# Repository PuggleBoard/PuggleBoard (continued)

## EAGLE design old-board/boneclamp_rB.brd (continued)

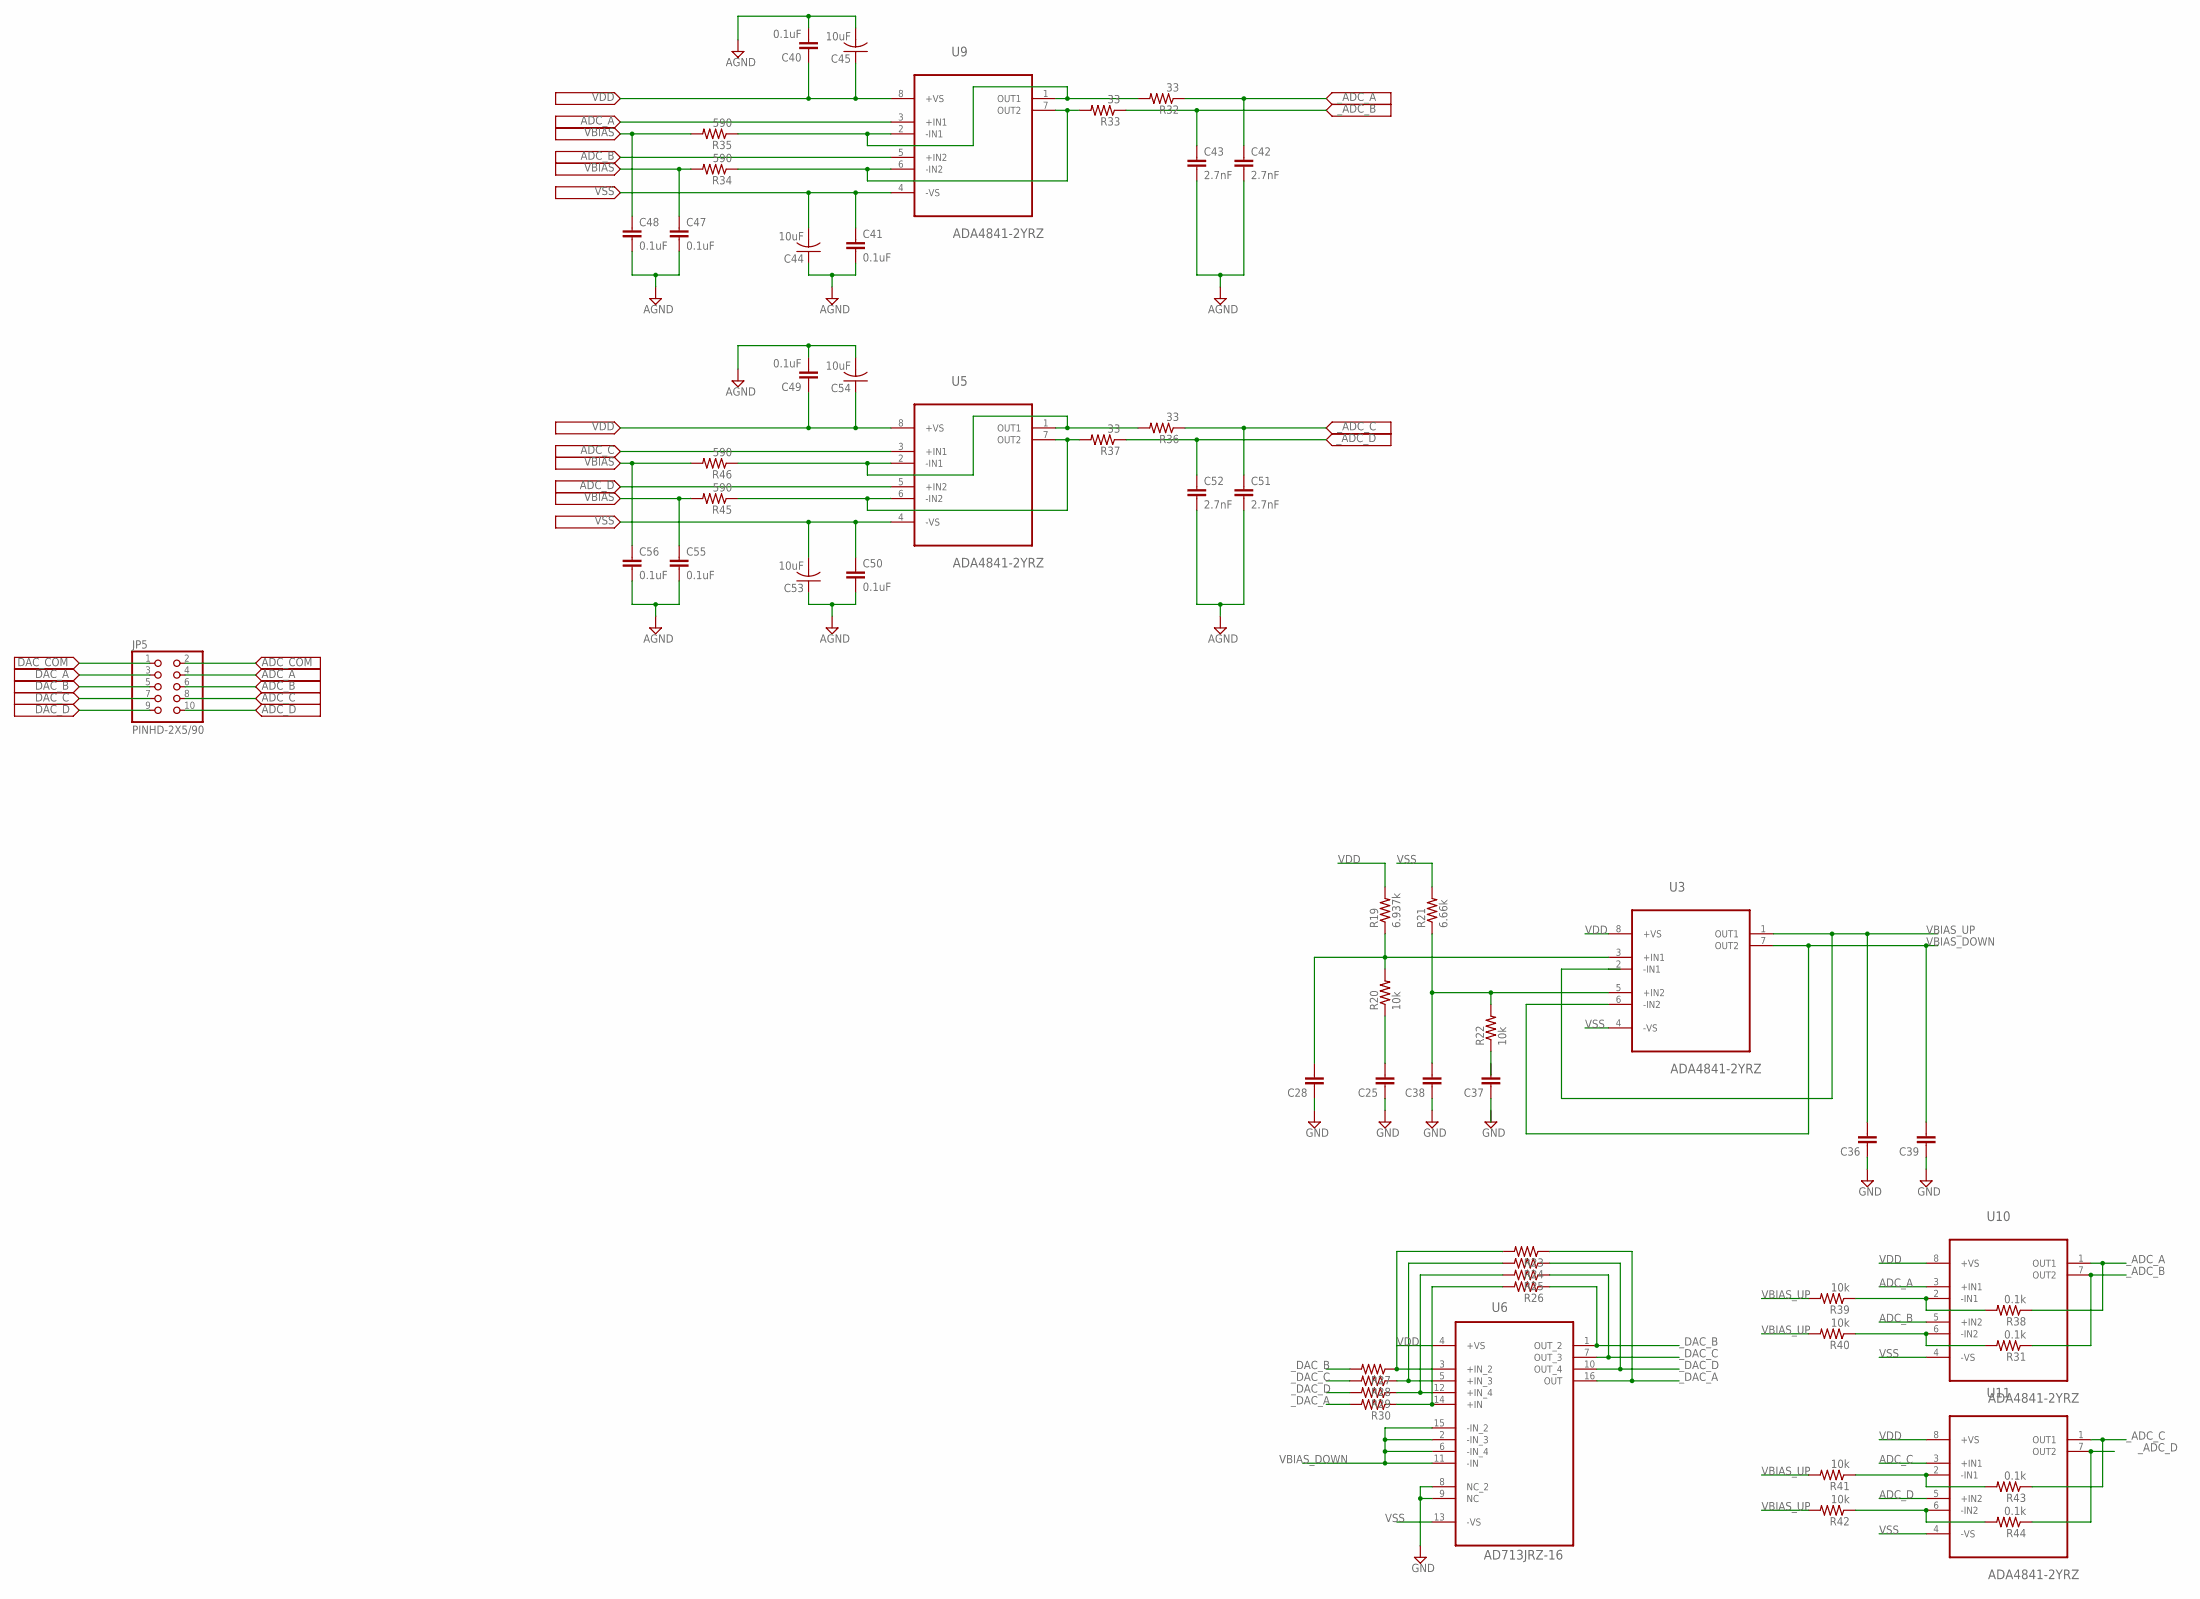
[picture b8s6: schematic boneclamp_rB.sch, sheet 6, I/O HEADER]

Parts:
C25, C28, C36, C37, C38, C39: C-EU025-025X050; C025-025X050
C40, C41, C47, C48, C49, C50, C55, C56: 0.1uF; C0805
C42, C43, C51, C52: 2.7nF; C0805
C44, C45, C53, C54: 10uF; C0805
JP5: PINHD-2X5/90; 2X05/90
R19: 6.937k; 0204V
R20, R22: 10k; 0204V
R21: 6.66k; 0204V
R23, R24, R25, R26, R27, R28, R29, R30: R-US_0204/2V; 0204V
R31, R38, R43, R44: 0.1k; R0805
R32, R33, R36, R37: 33; R0603
R34, R35, R45, R46: 590; R0603
R39, R40, R41, R42: 10k; R0805
U3, U5, U9, U10, U11: ADA4841-2YRZ; SOIC127P600X175-8N
U6: AD713JRZ-16; SOIC127P1032X265-16N

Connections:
ADC_A: JP5.4, U9.3 (+IN1), U10.3 (+IN1)
ADC_B: JP5.6, U9.5 (+IN2), U10.5 (+IN2)
ADC_C: JP5.8, U5.3 (+IN1), U11.3 (+IN1)
ADC_COM: JP5.2
ADC_D: JP5.10, U5.5 (+IN2), U11.5 (+IN2)
AGND: C40.2, C41.2, C42.2, C43.2, C44.1, C45.2, C47.2, C48.2, C49.2, C50.2, C51.2, C52.2, C53.1, C54.2, C55.2, C56.2; also elsewhere on the board
DAC_A: JP5.3
DAC_B: JP5.5
DAC_C: JP5.7
DAC_COM: JP5.1
DAC_D: JP5.9
GND: C25.1, C28.1, C36.1, C38.1, C39.1, U6.8 (NC_2), U6.9 (NC); also elsewhere on the board
unnamed: R37.2, R45.1, U5.6 (-IN2), U5.7 (OUT2)
unnamed: R33.2, R34.1, U9.6 (-IN2), U9.7 (OUT2)
unnamed: R26.2, R30.1, U6.14 (+IN)
unnamed: R36.2, R46.1, U5.1 (OUT1), U5.2 (-IN1)
unnamed: R32.2, R35.1, U9.1 (OUT1), U9.2 (-IN1)
unnamed: R25.2, R29.1, U6.12 (+IN_4)
unnamed: C38.2, R21.1, R22.2, U3.5 (+IN2)
unnamed: C28.2, R19.1, R20.2, U3.3 (+IN1)
unnamed: R24.2, R28.1, U6.5 (+IN_3)
unnamed: R23.2, R27.1, U6.3 (+IN_2)
unnamed: C25.2, R20.1
VBIAS: C47.1, C48.1, C55.1, C56.1, R34.2, R35.2, R45.2, R46.2; also elsewhere on the board
VBIAS_DOWN: C39.2, U3.6 (-IN2), U3.7 (OUT2), U6.2 (-IN_3), U6.6 (-IN_4), U6.11 (-IN), U6.15 (-IN_2)
VBIAS_UP: C36.2, R31.2, R38.2, R39.1, R39.2, R40.1, R40.2, R41.1, R41.2, R42.1, R42.2, R43.2, R44.2, U3.1 (OUT1), U3.2 (-IN1), U10.2 (-IN1), U10.6 (-IN2), U11.2 (-IN1), U11.6 (-IN2)
VDD: C40.1, C45.1, C49.1, C54.1, R19.2, U3.8 (+VS), U5.8 (+VS), U6.4 (+VS), U9.8 (+VS), U10.8 (+VS), U11.8 (+VS); also elsewhere on the board
VSS: C41.1, C44.2, C50.1, C53.2, R21.2, U3.4 (-VS), U5.4 (-VS), U6.13 (-VS), U9.4 (-VS), U10.4 (-VS), U11.4 (-VS); also elsewhere on the board
_ADC_A: C42.1, R32.1, R38.1, U10.1 (OUT1); also elsewhere on the board
_ADC_B: C43.1, R31.1, R33.1, U10.7 (OUT2); also elsewhere on the board
_ADC_C: C51.1, R36.1, R43.1, U11.1 (OUT1); also elsewhere on the board
_ADC_D: C52.1, R37.1, R44.1, U11.7 (OUT2); also elsewhere on the board
_DAC_A: R23.1, R30.2, U6.16 (OUT); also elsewhere on the board
_DAC_B: R26.1, R27.2, U6.1 (OUT_2); also elsewhere on the board
_DAC_C: R25.1, R28.2, U6.7 (OUT_3); also elsewhere on the board
_DAC_D: R24.1, R29.2, U6.10 (OUT_4); also elsewhere on the board

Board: 4 copper layers, 136 parts (0 on the bottom side), 59 nets, no tracks yet.

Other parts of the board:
U$77: ADS8343; SOP63P500X150-16N

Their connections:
GND: U$77.10, U$77.11; also elsewhere on the board
VCC: U$77.1, U$77.9

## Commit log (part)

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2013-02-24 Renamed the pcb folder to be more in line with other directory names
2013-02-24 Started working through the basic wiring on the schematic, connectrating on grounds, power, and analog IO
2013-02-27 I put an anti-aliasing filter design tool, provided by TI, into the PCB folder. The stop frequency (the frequency at which the attenuation is equal to the noise floor of the ADC (NOT the -3 dB point)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
2013-03-03 Found a good regulator for powering the BB using the +/- 6 to 12 volt rails required to use the boneclamp. Updated schematic and added data sheet to data-sheets folder
2013-03-03 Renamed file
2013-03-03 Added EEPROM to the I2C2bus to follow standard daughter board device ID requirements
2013-03-03 Added external 2.5 volt references for DAC and ADC. This circuit needs a buffer option which can be feed into the 3 position jumper.
2013-03-09 Moved the proto list directory to its proper location
2013-03-09 More changes to circuit
2013-03-09 Orgnanized data sheets
2013-03-09 Worked a bit on the schematic
2013-03-10 Added extended linear technologies library
2013-03-10 Added data sheet for +5V LDO reg.
2013-03-10 Minor schematic edit
2013-03-11 Added data sheets for the smd-to-dip adapters we will use. Minor changes to schematic
2013-03-12 Moved BOMs to their own directory
2013-03-13 Updated adafruit library with 2X5 0.1 inch pitch header, which we will use for I/O on the BC. Added that to the schematic
2013-03-14 Added buffered VREF divider, which feeds back into ADC to get bipolar input swing.
2013-03-14 Removed obsolete design-notes file
2013-03-15 Minor fixed to EEPROM circuit and ADC VREF buffer. Stephano, don't kill me.
2013-03-15 Added evaluation board PDFs to the data-sheets folder
2013-03-17 Minor edit
2013-03-18 Added p6 to the schematic of the BB, update the BC shematic and board
2013-03-19 Added Ground and power plane to pcb. Power plane will need to be split into primarly VDD and then a bit at the front of the board for VSS. VDD and VSS planes should not overlap in the Z direction.
2013-03-23 Added Stefano's biasing circuitry back into the master branch schematic. Automatic merge was not going to work properly
2013-03-23 Fixed the input biasing scheme. The op-amps we are using require -0.25 to 5.2 volt supply range to push the inputs into the 0 to 4.096 range required by the ADC. This means that our positive rail is 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
2013-03-23 Added pinout info for the bus pirate. Created a logic-sniffer project to examine the SPI signals sent to the chips. DAC is working nicely.
2013-03-24 Added information on the lm2663 DC-DC switch capacitor voltage inverter. A much better option than the inductor based inverter we are currently using.
2013-03-25 Added yet another option to explore for the ADC. I need to make some calls to find out what the best option is. There is always something wrong with any particular choice.
2013-03-26 Added the 8331 to schematic. I'm pretty sure this is the right ADC.
2013-03-27 Added excellent choice for external 2.048 VREF. This data sheet includes the circuit for creating a bipolar reference.
2013-03-31 Added data sheet for MCP8024 in the proto folder. This ADC will be helpful for troubleshooting the SPI interface since it is low cost and easy to play with.
2013-04-01 Finished basics of input stage to new 8331 and some of the digital interface for it.
2013-04-01 Minor changes.
2013-04-06 Tagged v0.1 as the last version to contain an effort to implement daisy chaining. This can serve as point of reference if we want to revisit that in the future.
2013-04-06 Cleaned up schematic to get it ready for actual component selection (passive commoponent packages) and final wiring.
2013-04-06 Replaced negative LDO with the MAX1735.
2013-04-07 Uninverted DAC output bias, found alternative amp
2013-04-07 Nearly finished with full circuit.I need the GPIO pins that we will be using.
2013-04-08 Minor schematic changes.
2013-04-18 Repackaged passive components.
    Shrank all passive components, verified their viability.
2013-04-19 Took care of most of Amanda's comments. Started using data buses instead of individual nets for the SPI interfaces.
2013-04-20 Started renaming test points, etc.
2013-04-20 Started getting rid of signal tag symbols, take too much room and cause problems with automatic component renumbering.
2013-04-20 Schematic nearly done. Checking/updating BOM.
2013-04-20 Finished BOM.
2013-04-20 Started layout.
2013-04-21 Finished switching voltage inverter layout.
2013-04-21 Added split GND plane.
2013-04-26 Committed breakout board
2013-05-02 Started laying out the AO buffer stage.
2013-05-02 Minore changes.
2013-05-03 Finalizing DAC/ADC buffer layout.
2013-05-03 Halfway through analog filters.
2013-05-04 Working on mixed signal ICs/
2013-05-04 Fixed the ground planes.
2013-05-06 DAC bypassing complete.
2013-05-09 Started to route IC groups together.
2013-05-10 More routing.
2013-05-10 Routing almost complete.
2013-05-11 Finished first intetation of routing! Need to clean up the silkscreen, check for single ended wires, double check schematic wiring, run DRC, and send it to fab.
2013-05-12 Fixed some random problems with the silkscreen.
2013-05-12 More minor silkscreen issues. Started drawing logo.
2013-05-12 Adding 4th DAC SPI pin on GPIO1_13
2013-05-12 Re-added the DAC SDO line.
2013-05-12 Added logo to board.
2013-05-12 Created CAM job to work with OSH Park.
2013-05-12 Reorganizing.
2013-05-12 Renamed the board.
2013-05-12 Finished the silkscreen stuff.
2013-05-13 Updated readme.
2013-05-15 Finished BOB.
2013-05-16 Finished BOB, created gerber files.
2013-05-16 Name change because versioning should happen via tags, not file names.
2013-05-16 Minor.
2013-05-19 Fixed the ribbon cable mapping to take into account reflective symmetry.
2013-05-20 Almost done actually fixing GPIO mapping for PRU1
2013-05-20 Routed the SPI busses to GPIO pins accessible by PRU1.
2013-05-20 Fixed BOMs
2013-05-20 Added a CAM job to process a solder stencil for the board.
2013-05-24 Ready to print v0.1
2013-05-28 Fixed BOM for v1.0
2013-06-04 Added OSH Park board renders.
2013-06-08 Added eeprom Javascript Object Notation (.json) file containing cape metadata.
2013-06-12 Made simple case for the bb/pg combo.
2013-06-20 Started a document with a list of improvements to be implemented for next board revision.
2013-06-23 Updated v1.0 assembly notes.
2013-06-25 Started implementing changes from first build.
2013-06-30 More notes on 1v0 build.
2013-07-05 Added a note.
2013-07-08 Added simulation files.
2013-07-19 More documentation and minimal acqusition time (time between CONVST signals) calculations.
2013-07-21 Started to revise board.
2013-07-22 Added a couple more notes.
2013-07-26 More board mods and design notes.
2013-07-29 Cleanup.
2013-08-02 Started laying out v2.0.
2013-08-03 Added OPA209 Datasheet to used folder.
2013-08-04 Finished op-amp pattern for ADC Buffer.
2013-08-04 Laying out relative positions of functional modules (e.g power, regulation, buffer, conversion, etc).
2013-08-05 Added a couple notes.
2013-08-05 Relaced through-hole header for GPIO with HDMI connector. This board will be intan ready.
2013-08-05 Made a package for the uModule inverter.
2013-08-06 Replaced swiching inverter with uModule. Removed external power option.
2013-08-06 More layout.
2013-08-07 Nearly done with split-plane version.
2013-08-07 Intial layout complete. Time to clean up DRC errors.
2013-08-07 Should be done. Going to check with fresh eyes before tagging and getting gerbers ready.
2013-08-07 Board/schematic documentation.
2013-08-07 Minor changes. Trying to work out attributes for parts so that making a BOM is more automated.
2013-08-08 Switched from HDMI connector to standard ribbon since this has better impedance characterisitics for single-ended digital signals.
2013-08-08 Started differential routing on Intan BOB.
2013-08-09 All that needs to be done is silk-screen work.
2013-08-09 LDVS conversion board complete.
2013-08-12 Many final changes to design before fabrication.
2013-08-12 Added a CMOS to TTL BOB.
2013-08-13 Finished CMOS to TTL BOB. Cleaned up directory structure.
2013-08-13 Added back missing board file.
2013-08-13 More cleanup.
2013-08-14 Started looking into BOM-EX ULP for part database managment. Not sure if this is the right choice.
2013-08-16 For real this time. I have decided to use the BOM-AM.ULP parts managment program. I rebased the parts database to its format and started a global parts database in the ./parts folder.
2013-08-16 Finished BOMs (and integrated parts into database) for all the BOBs. Now must do for the main board. Will take a while.
2013-08-18 Almost done with DK BOMs. Still a few problems: (1) There are some parts (e.g. 46 pin headers) that do not appear as individual components since they are included with the BB device that need to be m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
2013-09-10 Some of the resistors were specified as a 0201 package. Changed to 0603.
2013-09-22 Started a file to document issues with PuggleBoard v2.0 assembly.
2013-09-26 Fixed issue three in board/doc/notes_2v0-assembly.
2013-10-02 Added note about the misbehaving SPI line.
2013-10-03 Added more notes on opamp selection.
2013-10-11 Updated some missing powe connections.
2013-10-17 Added photo of v2.0 PCB.
2013-10-24 Added initial artwork fro Intan display.
2013-10-27 Moving along on display for conferences.
2013-10-27 Almost done with PuggleBoard display.
2013-10-28 Finished first version of display flyer and made the laser cutter paths for case.
2013-10-28 Really final touches.
2013-10-31 Final touches to artwork.
2013-11-06 Added a note about REF cap choice for DAC.
2013-11-06 Added png versions of artwork.
2013-11-06 Remade flyer png in higher rez.
2013-11-18 Moved the art folder to the Art repo.
2013-11-19 Fixed V_Ref bypass cap for DAC.
2013-11-22 Almost done with 2v0 board changes. Getting ready for 2.1 fabrication.
2013-11-22 PuggleBoard version 2.1. Created gerbers and placed order.
2013-11-25 Finished up v2.0 assembly notes.
2014-02-16 Add a Bitdeli badge to README
2014-04-03 Started documenting and addressing Edgar's comments.
2014-04-18 adding TI specific BOM
2014-04-21 Fixed a couple more op-amp symbols.
2014-04-21 Added new Beaglebone pinouts.
2014-04-22 Added block level proposed layout for r3.0
2014-04-24 Added additional ferrite chip on +5V rail from BB, fixed some other minor stuff.
2014-04-30 Fixed the flipped pin on the MISO LVDS module that Yogi found.
2014-05-06 Started laying out new board.
2014-05-07 Board layout.
2014-05-17 Added sync circuit. Continuing layout.
2014-05-18 Nearly finished with layout. Need to get digital planes and LVDS signals routed. Hard parts done.
2014-05-19 Minor schematic cleanup.
2014-05-21 More digital routing.
2014-05-21 Fixed a few DRC errors.
2014-05-22 Did some of the differential pair wiring.
2014-05-22 updated digital lines with new pinout; EEPROM still using pins 19 and 20
2014-05-22 Board is ready for Edgar to look at. There is one strange DRC error, but that can be resolved later. Also, silk screens are a mess, but Edgar can see the layout at least.
2014-05-29 Impletemented Edgar's suggestions from our meeting. Should be nearing the silkscreen finalization stage.
2014-05-29 Minor improvements. Reverted back to old board shape since we are not using the upper right corner for anything.
2014-05-30 Finished top layer silkscreen. Moved ground points on decoupling capacitors to beneath the pad. This will result in a DRC error, but I saw an analog devices eval board doing this. It makes sense and 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
2014-05-30 R3.0 is essentially finished. Need to double check the full circuit before printing.
2014-05-31 Repo cleanup.
2014-05-31 Added all relevant data sheets to the repo.
2014-05-31 Created gerbs. More cleanup.
2014-06-04 Switched out the LTM8045 inverter for a much lower cost, TI based solution. The LTM was not avaiable for less than 22 dollars each from Newark. This solution is about 5 dollars or so.
2014-06-04 Updated to new voltage inverter solution. Removed old data sheet.
2014-06-06 Finalized BOM. This is r3.0
2014-06-06 Added ground plane to bottom layer. Minor.
2014-06-23 Fixed a couple minor issues found while making the boards.
2014-07-10 Updated OSH Park design rules.
